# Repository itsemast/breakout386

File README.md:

# Breakout386

This project was inspired by the [Hand386 computer](https://yeokhengmeng.com/2023/06/teardown-and-review-of-hand386/), and it will reuse the same base components, but instead of a handheld device, it's going to be an extremely light SBC. By stripping down all extras (battery, screen, keyboard, graphics card, sound card, USB interface), it's possible to make the PCB design simple and low-cost. All the interfaces provided by the SoC will be broken out to expansion connectors, so all the extras can still be added as expansion cards.

The goals of this project are: simplicity, extandability and reusing old components as much as possible. Surface mount components are prefered over their through-hole counterparts, except for connectors.

# Specs

- M6117D SoC (M1386SX CPU + M1217B chipset)
- *TBD* DRAM
- *TBD* CMOS Flash (BIOS)
- ISA bus for expansion cards
- IDE interface for storage media
- PS/2 interface for keyboard and mouse
- PC speaker
- RTC battery
- GPIO
- 5V power input

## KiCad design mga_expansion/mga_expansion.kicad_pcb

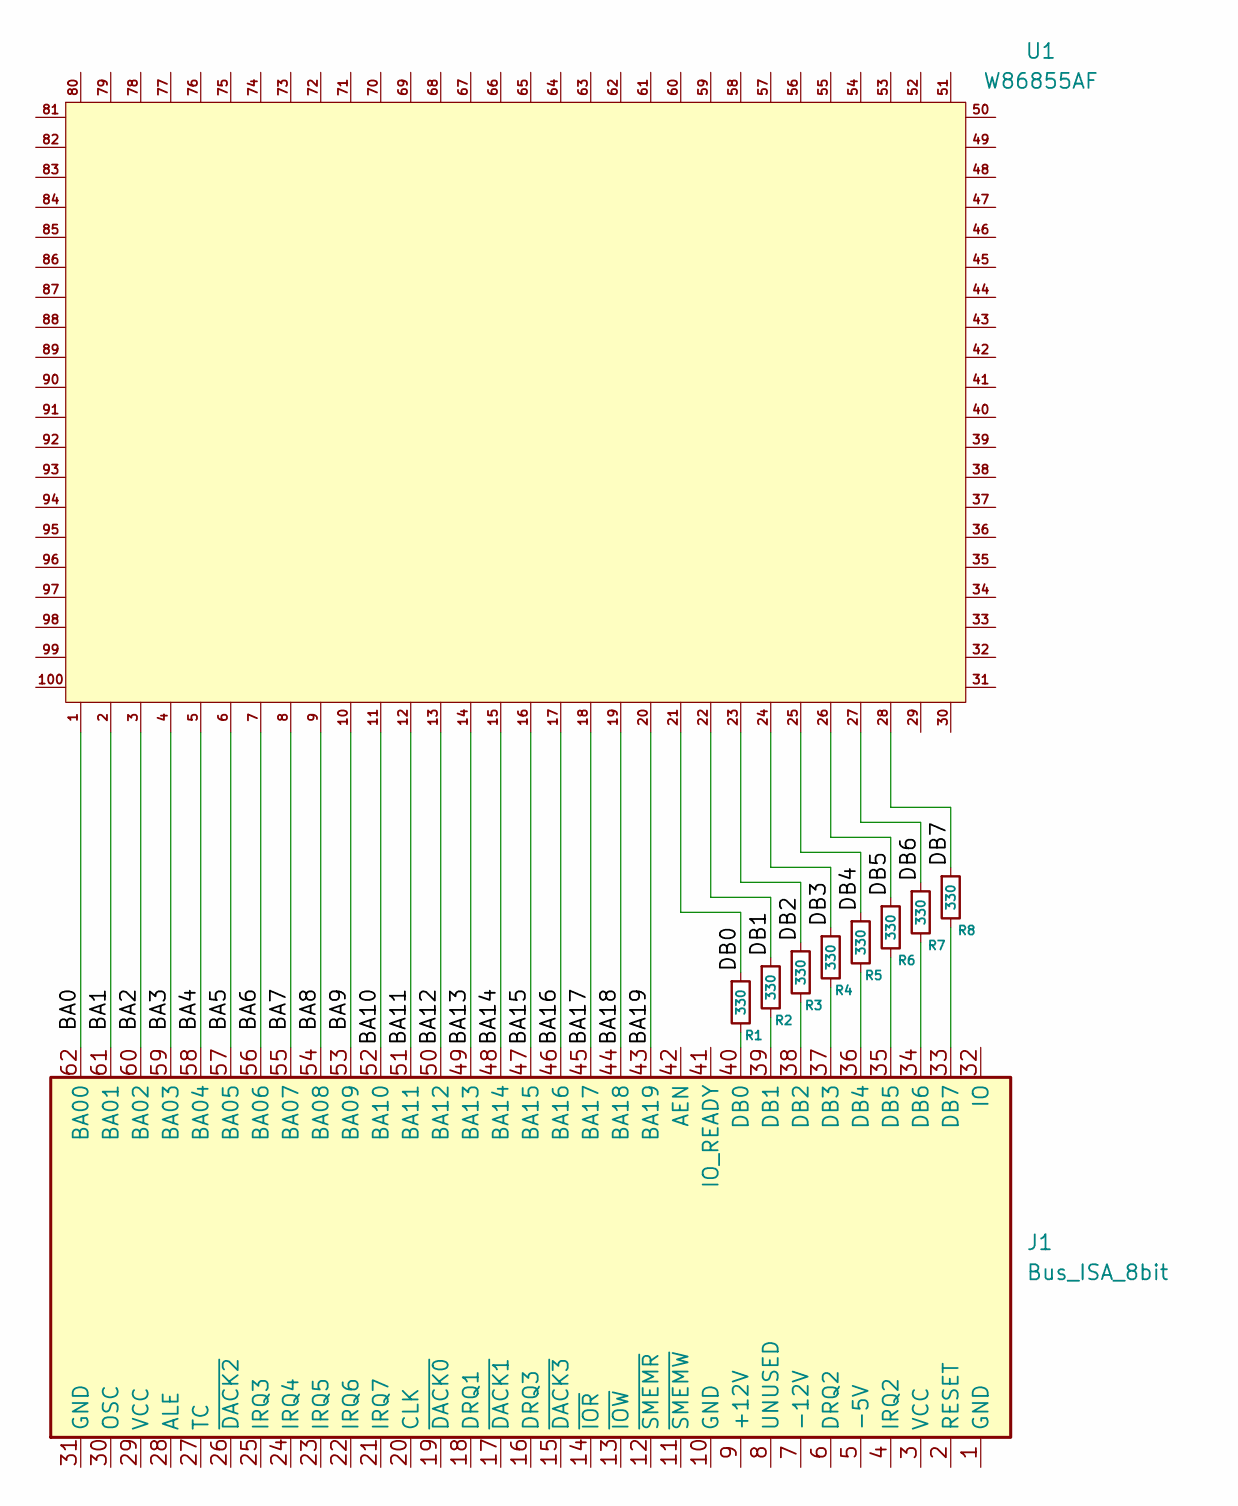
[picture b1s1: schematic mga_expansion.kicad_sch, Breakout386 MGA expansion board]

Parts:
J1: Bus_ISA_8bit; BUS_XT
R1, R2, R3, R4, R5, R6, R7, R8: 330; R_Axial_DIN0207_L6.3mm_D2.5mm_P10.16mm_Horizontal
U1: W86855AF; PQFP-100_14x20mm_P0.65mm

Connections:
/BA0: J1.62 (BA00), U1.1
/BA1: J1.61 (BA01), U1.2
/BA2: J1.60 (BA02), U1.3
/BA3: J1.59 (BA03), U1.4
/BA4: J1.58 (BA04), U1.5
/BA5: J1.57 (BA05), U1.6
/BA6: J1.56 (BA06), U1.7
/BA7: J1.55 (BA07), U1.8
/BA8: J1.54 (BA08), U1.9
/BA9: J1.53 (BA09), U1.10
/BA10: J1.52 (BA10), U1.11
/BA11: J1.51 (BA11), U1.12
/BA12: J1.50 (BA12), U1.13
/BA13: J1.49 (BA13), U1.14
/BA14: J1.48 (BA14), U1.15
/BA15: J1.47 (BA15), U1.16
/BA16: J1.46 (BA16), U1.17
/BA17: J1.45 (BA17), U1.18
/BA18: J1.44 (BA18), U1.19
/BA19: J1.43 (BA19), U1.20
/DB0: R1.1, U1.21
/DB1: R2.1, U1.22
/DB2: R3.1, U1.23
/DB3: R4.1, U1.24
/DB4: R5.1, U1.25
/DB5: R6.1, U1.26
/DB6: R7.1, U1.27
/DB7: R8.1, U1.28
unnamed: J1.40 (DB0), R1.2
unnamed: J1.39 (DB1), R2.2
unnamed: J1.38 (DB2), R3.2
unnamed: J1.37 (DB3), R4.2
unnamed: J1.36 (DB4), R5.2
unnamed: J1.35 (DB5), R6.2
unnamed: J1.34 (DB6), R7.2
unnamed: J1.33 (DB7), R8.2

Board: 2 copper layers, 10 parts (0 on the bottom side), 36 nets, no tracks yet.

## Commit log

2024-03-29 rename the sheets for a new project
2024-03-29 add M6117D library symbol
2024-03-29 add a library with retro connectors symbols
2024-03-29 initial connection of ISA, IDE and RAM
2024-03-29 add speaker, keyboard, mouse and power connectors
2024-03-30 connect IRQ9 to ISA bus
2024-03-30 add a CMOS flash for BIOS
2024-03-30 connect IDE address lines to the bus
2024-03-30 rearrange connectors and flash chip
2024-03-30 connect CMOS flash to X-bus
2024-03-30 replace 8 bit ISA with 16 bit
2024-03-30 connect additional signals to 16 bit bus
2024-04-01 add MGA expansion board
2024-04-01 rename the sheets for the new board
2024-04-01 add initial symbol for W86855AF reverse engineering
2024-04-01 connect ISA address and data lines
2024-04-01 add XT bus edge connector footprint
2024-04-01 assign footprints to ISA connector and resistors
2024-04-01 initial board outline and component placement
2024-04-01 add RAM and ROM chips
2024-04-01 add a library of old SRAM and DRAM
2024-04-01 add PLCC-18 footprint for 4464 DRAM
2024-04-18 trace RAM pinout according to memory datasheet
